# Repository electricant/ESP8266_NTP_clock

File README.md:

# ESP8266_NTP_clock
Very basic bedside digital clock using the NTP8266 to sync the time using NTP.

## Features

This started as a whish list and expanded during development. Since this is an
open-ended project this list may grow. Never settle!

 * Synchronize time using my local network NTP server
 * Receive and display temperature and humidity readings from my external
   weather station. This way I know at a glance how to get dressed in the
   morning.
 * Backlight support either triggered by a button or automating using a
   photoresistor
 * DST support without requiring an external library

## Firmware

Required libraries:
 * PubSubClient
 * TimeLib
 * ArduinoJson
 * [qd_sched](https://github.com/electricant/qd_sched) - simple scheduler for repetitive tasks

The code uses a local, improved version of the EasyNTPClient library. It is
available as a git submodule.

## PCB/Mechanical assembly

There's not much to it actually. Just a PCB the same size of the display.
The display board and the control PCB are sandwiched together using M2.5 hex
standoffs. The display conencts to the mainboard using 2.54mm headers.

## Pictures

3D rendering of the PCB:

Prototype (I swear it is not a bomb officer):

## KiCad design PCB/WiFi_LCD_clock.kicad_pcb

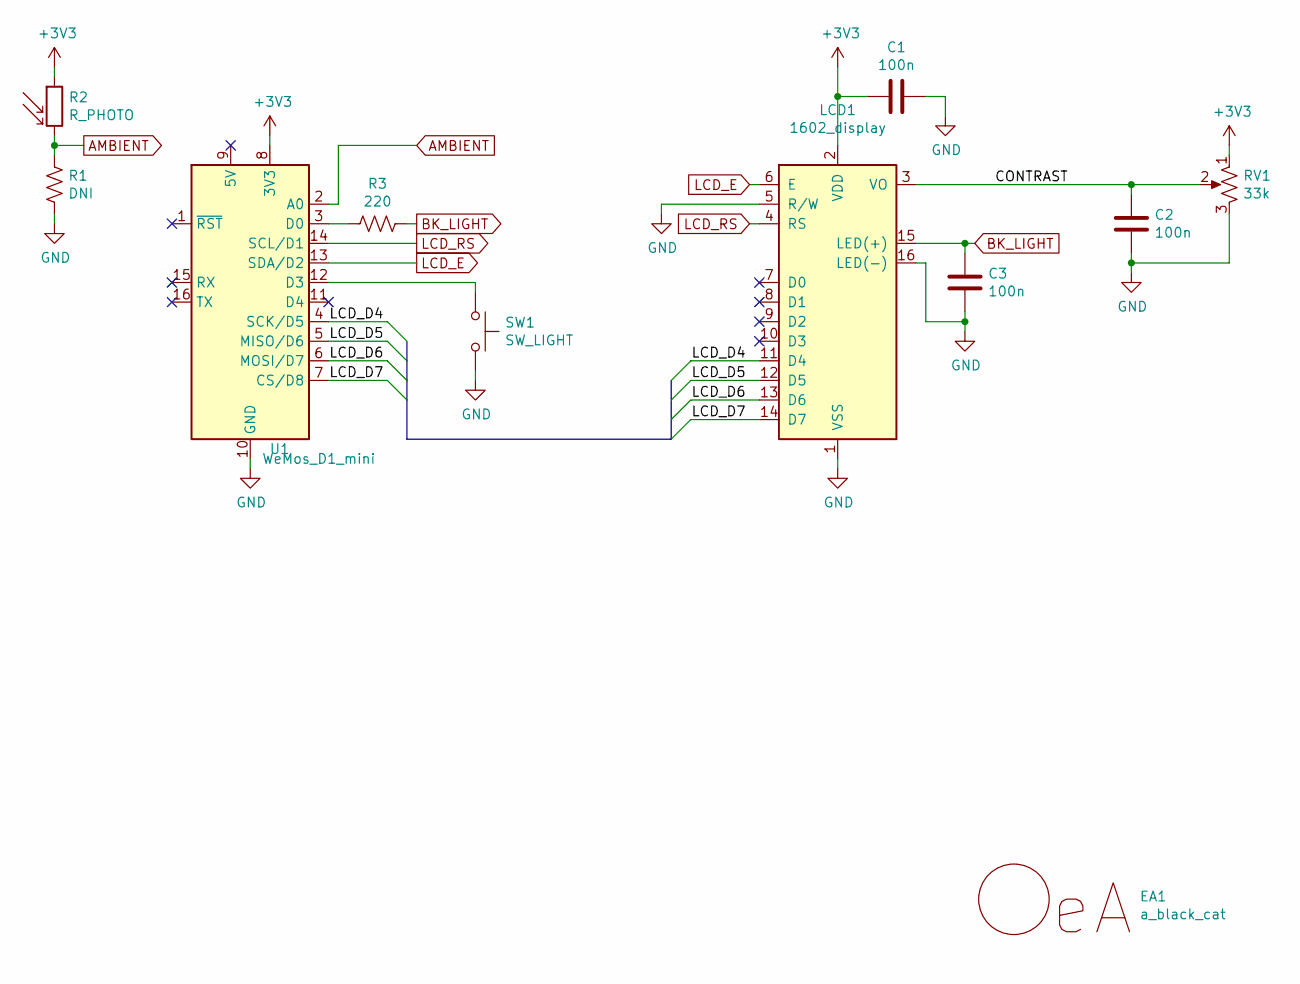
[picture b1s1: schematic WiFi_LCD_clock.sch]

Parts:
C1, C2, C3: 100n; universal_cap
EA1: a_black_cat
LCD1: 1602_display; 1602_lcd
R1: DNI; universal_res
R2: R_PHOTO; R_LDR_4.9x4.2mm_P2.54mm_Vertical
R3: 220; universal_res
RV1: 33k; Potentiometer_Piher_PT-6-V_Vertical
SW1: SW_LIGHT; SW_PUSH_6mm
U1: WeMos_D1_mini; WEMOS_D1_mini_light

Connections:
+3V3: C1.2, LCD1.2 (VDD), R2.1, RV1.1, U1.8 (3V3)
/CONTRAST: C2.1, LCD1.3 (VO), RV1.2
/LCD_D4: LCD1.11 (D4), U1.4 (SCK/D5)
/LCD_D5: LCD1.12 (D5), U1.5 (MISO/D6)
/LCD_D6: LCD1.13 (D6), U1.6 (MOSI/D7)
/LCD_D7: LCD1.14 (D7), U1.7 (CS/D8)
AMBIENT: R1.1, R2.2, U1.2 (A0)
BK_LIGHT: C3.1, LCD1.15 (LED(+)), R3.1
GND: C1.1, C2.2, C3.2, LCD1.1 (VSS), LCD1.5 (R/W), LCD1.16 (LED(-)), R1.2, RV1.3, SW1.2, U1.10 (GND)
LCD_E: LCD1.6 (E), U1.13 (SDA/D2)
LCD_RS: LCD1.4 (RS), U1.14 (SCL/D1)
unnamed: R3.2, U1.3 (D0)
unnamed: SW1.1, U1.12 (D3)

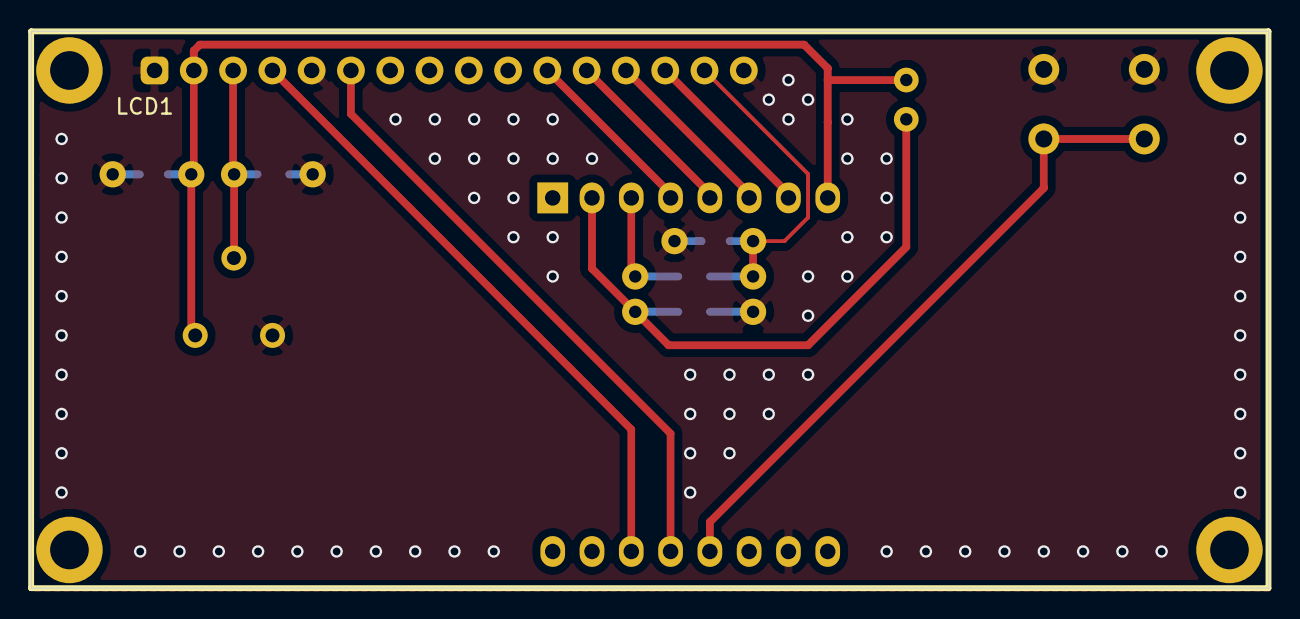
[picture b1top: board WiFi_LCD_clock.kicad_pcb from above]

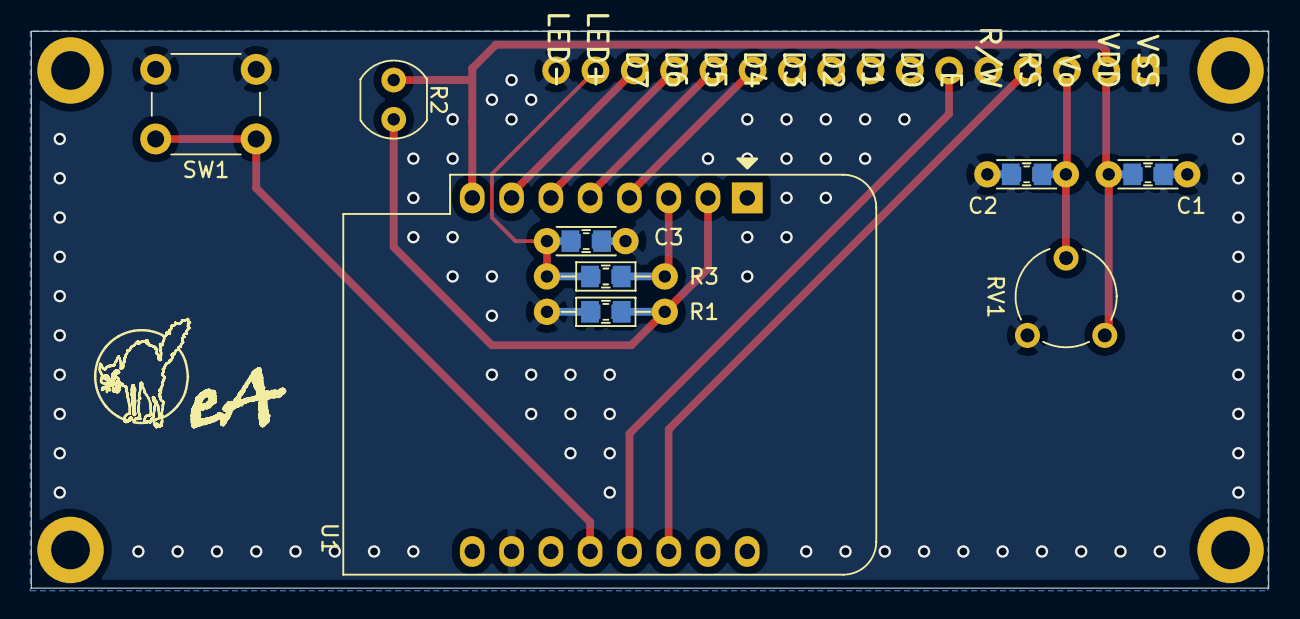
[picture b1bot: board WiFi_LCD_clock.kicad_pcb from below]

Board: 2 copper layers, 80.0 x 36.0 mm, 11 parts (10 on the bottom side), 13 nets.

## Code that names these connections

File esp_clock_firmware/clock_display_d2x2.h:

/*
 * Header file for the functions controlling the LCD display of the clock.
 *
 * It uses a 2x2 font for displaying the digits.
 *
 * The fonts are defined by a set of 8 custom chars which, combined, look like
 * digits. The custom chars are loaded when the display is initialized and are
 * defined by the chrN (0<= N < 8) arrays.
 * The way in which the custom chars are combined to form digits is defined in
 * the 'number_chars' array. This array has an entry for each digit. Within this
 * entry the index of the custom chars from left to right, top to bottom is present.	
 */
#ifndef CLOCK_DISPLAY_D2X2_H
#define CLOCK_DISPLAY_D2X2_H

#include <LiquidCrystal.h>
#include <pins_arduino.h>

/*
 * LCD pins definition. As seen in the schematic!
 */
#define LCD_RS D1
#define LCD_E  D2
#define LCD_D4 D5
#define LCD_D5 D6
#define LCD_D6 D7
#define LCD_D7 D8

// Global LCD instance
LiquidCrystal lcd = LiquidCrystal(LCD_RS, LCD_E, LCD_D4, LCD_D5, LCD_D6, LCD_D7);

/*
 * Custom chars
 */
byte chr0[] = {
  B01111,
  B11111,
  B11000,
  B11000,
  B11000,
  B11000,
  B11000,
  B11000
};
byte chr1[] = {
  B11110,
  B11111,
  B00011,
  B00011,
  B00011,
  B00011,
  B00011,
  B00011
};
byte chr2[] = {
  B11000,
  B11000,
  B11000,
  B11000,
  B11000,
  B11000,
  B11111,
  B01111
};
byte chr3[] = {
  B00011,
  B00011,
  B00011,
  B00011,
  B00011,
  B00011,
  B11111,
  B11110
};
byte chr4[] = {
  B11111,
  B11111,
  B00000,
  B00000,
  B00000,
  B00000,
  B00000,
  B00000
};
byte chr5[] = {
  B01111,
  B11111,
  B11000,
  B11000,
  B11000,
  B11000,
  B11111,
  B01111
};
byte chr6[] = {
  B11110,
  B11111,
  B00011,
  B00011,
  B00011,
  B00011,
  B11111,
  B11110
};
byte chr7[] = {
  B00000,
  B00000,
  B00000,
  B00000,
  B00000,
  B00000,
  B11111,
  B11111
};

byte number_chars[10][4] = {
  {0,  1,  2, 3}, // 0
  {1, 32,  3, 7}, // 1
  {4,  6,  5, 7}, // 2
  {4,  6,  7, 3}, // 3
  {2,  3, 32, 1}, // 4
  {5,  4,  7, 6}, // 5
  {5,  4,  2, 6}, // 6
  {4,  1, 32, 0}, // 7
  {5,  6,  2, 3}, // 8
  {5,  6,  7, 3}  // 9 
};

/*
 * Initialize the LCD display
 */
void lcd_init();

/*
 * Prints the given time on the LCD
 */
void lcd_print_time(uint8_t hrs, uint8_t mins);
void lcd_print_time(uint8_t hrs, uint8_t mins, uint8_t sec);

/*
 * Prints temperature and humidity
 */
void lcd_print_temp_humidity(float temp, float hum);

#endif

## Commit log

2021-04-01 Add Kicad PCB desing files.
2021-04-01 Add pictures of the PCB and the prototype
2021-04-01 Add some description and pictures to the readme
2021-04-01 Add clock firmware
2021-04-01 Update readme to ddescribe the firmwarea bit
2021-04-02 Fix deprecated BUILTIN_LED issue
2021-04-02 Tasks may not be scheduled if millis() overflows. Issue fixed
2021-04-02 Use a local copy of EasyNTPClient as a submodule
2021-04-04 move config files to their directory and the scheduler to its own files
2021-04-07 Use updated electricant/EasyNTPClient
2021-04-22 Add simple shell interface with some commands
2021-04-22 Add simple shell logging interface that uses a circular buffer
2021-04-22 Use the new logging interface
2021-04-22 Better CPU usage calculation using moving average
2021-04-26 Update code to the new PCB and use the ambient light sensor to control display backlight automatically
2021-04-29 Code refactoring and state machine for the backlight
2021-05-08 Turn off the builtin LED in case of error in deserializeJson
2021-12-06 Fix DST description since now it's working
2021-12-06 minor bugfixes
2021-12-07 Fix out of memory error when parsing json input string
2021-12-07 Minor tweaks to the logging stuff
2023-08-10 Make qd_sched an external library
2023-08-10 Minor tweaks
2023-08-19 Set MQTT keepalive according to MQTT_UPDATE_MS to allow longer MQTT loop intervals
2023-10-30 Rework DST logic a bit
